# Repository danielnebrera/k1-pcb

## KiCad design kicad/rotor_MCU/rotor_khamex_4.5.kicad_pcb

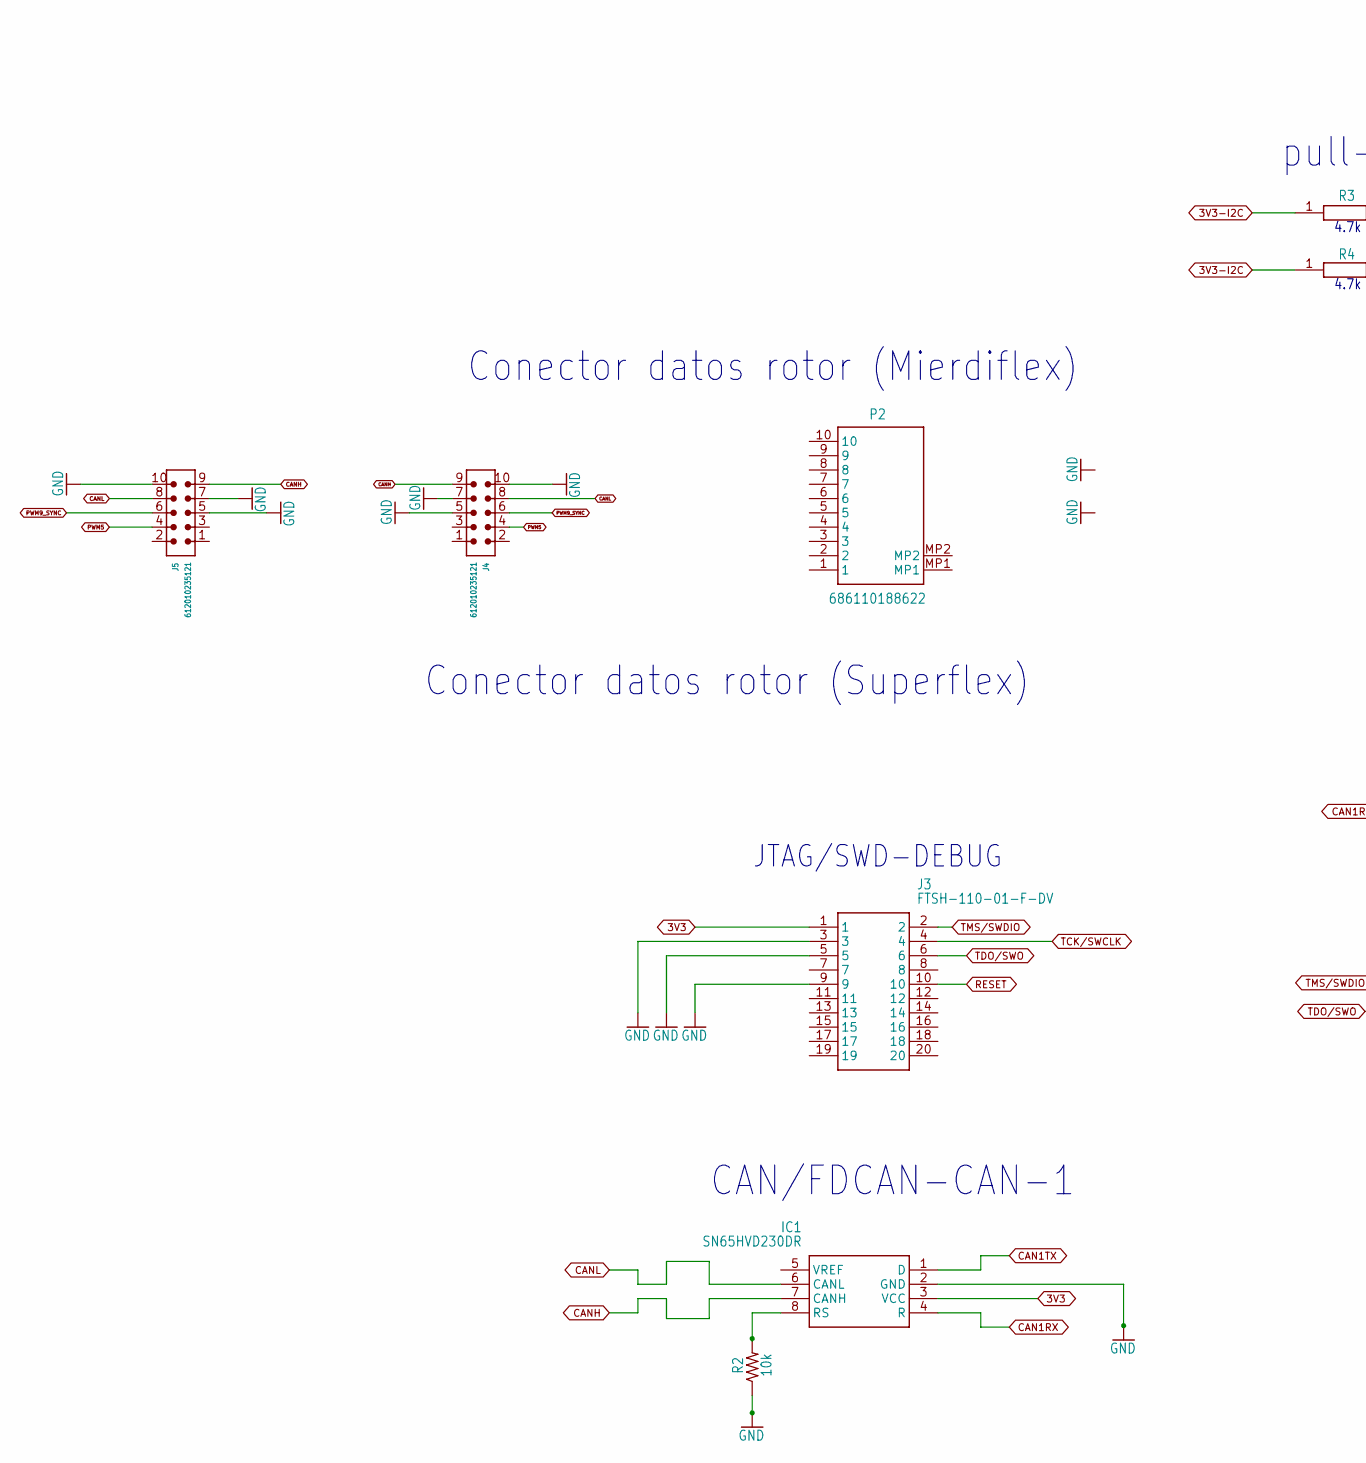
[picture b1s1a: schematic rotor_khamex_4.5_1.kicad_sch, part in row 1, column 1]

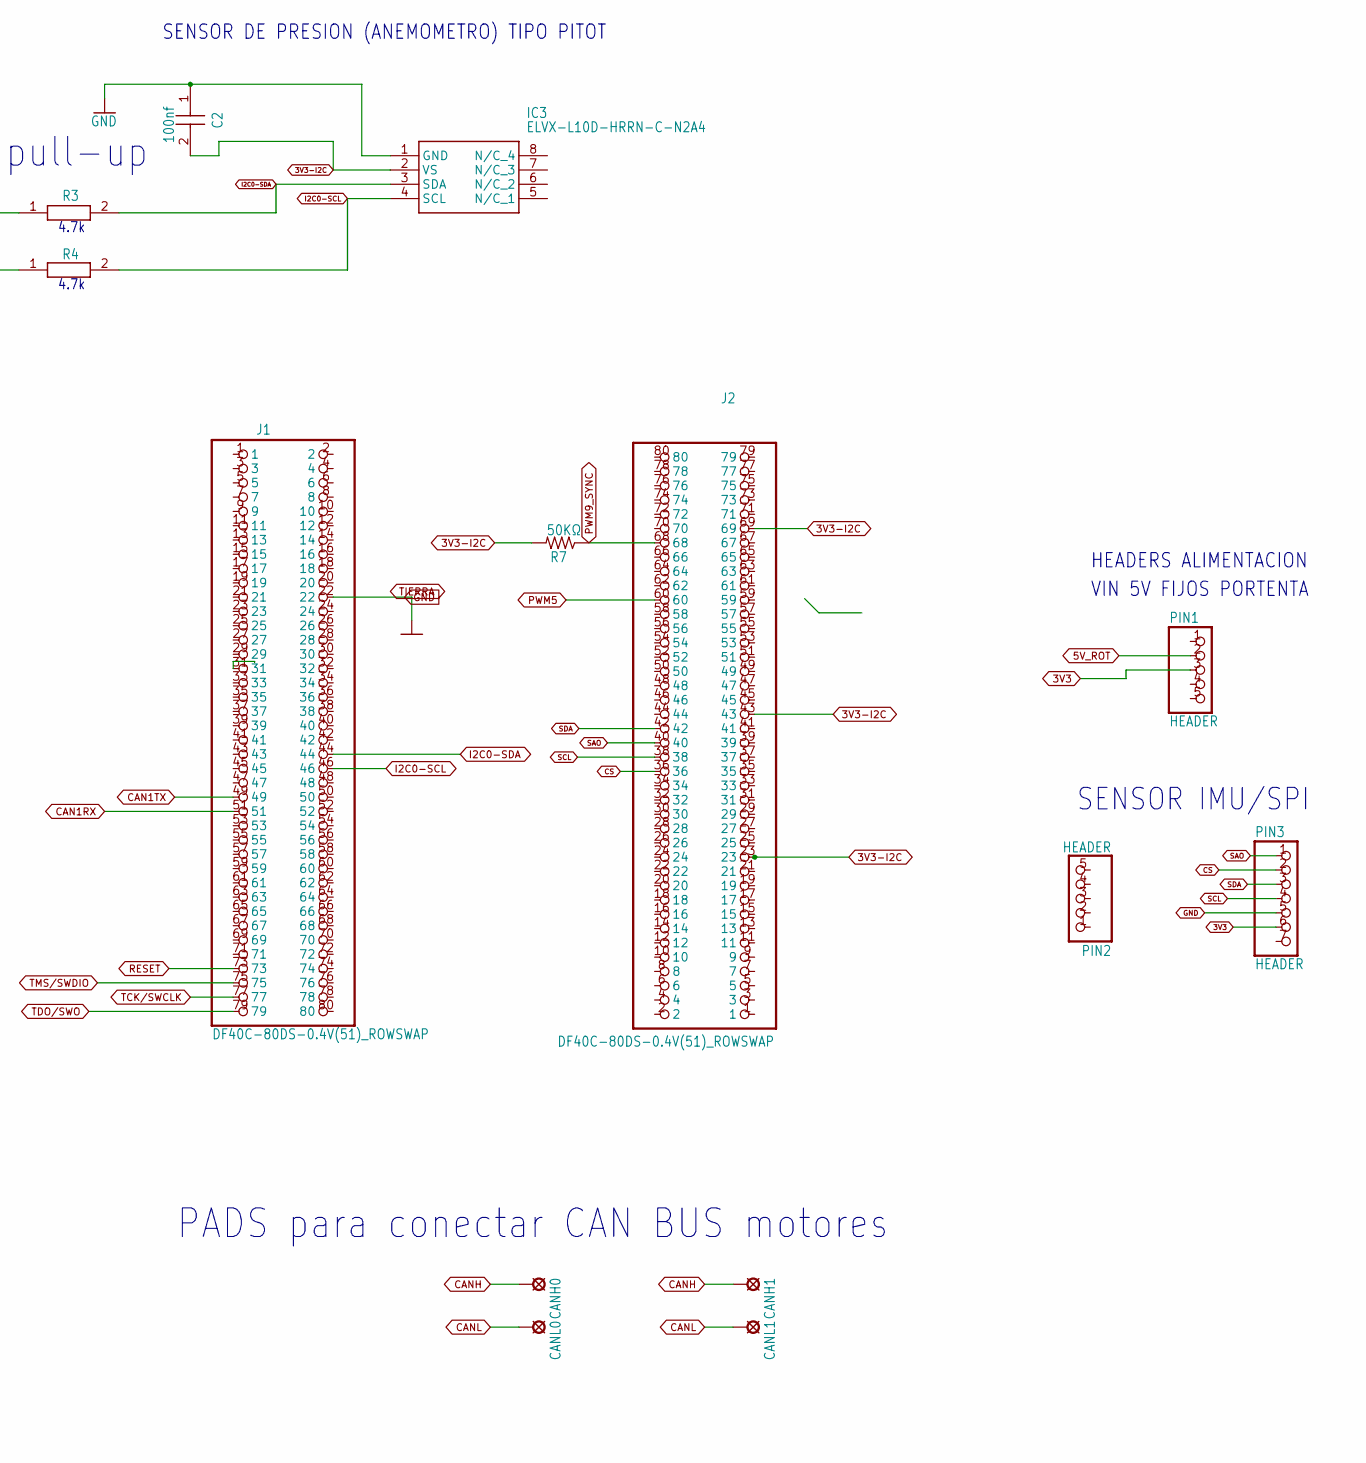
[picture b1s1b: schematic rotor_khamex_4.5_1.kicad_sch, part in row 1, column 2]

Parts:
C2: 100nf; CAPC2012X145N
CANH0, CANH1: LSP11
CANL0, CANL1: LSP11
IC1: SN65HVD230DR; SOT127P600X175-8N
IC3: ELVX-L10D-HRRN-C-N2A4; ELVXL10DHRRNCN2A4
J1, J2: DF40C-80DS-0.4V(51)_ROWSWAP; HRS_DF40C-80DS-0.4V(51)_ROWSWAP
J3: FTSH-110-01-F-DV; FTSH-110-XX-YYY-DV
J4, J5: 612010235121
P2: 686110188622
PIN1, PIN2: HEADER; 1X05
PIN3: HEADER; 1X07
R2: 10k; M0805
R3, R4: 4.7k; RESC2012X50N
R7: 50KΩ; M0805

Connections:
3V3: IC1.3 (VCC), J3.1, PIN1.3, PIN3.6
3V3-I2C: C2.2, IC3.2 (VS), J2.23, J2.43, J2.69, R3.1, R4.1, R7.2
5V_ROT: PIN1.2; also elsewhere on the board
CAN1RX: IC1.4 (R), J1.51
CAN1TX: IC1.1 (D), J1.49
CANH: CANH0.MP, CANH1.MP, IC1.7 (CANH), J4.9, J5.9
CANL: CANL0.MP, CANL1.MP, IC1.6 (CANL), J4.8, J5.8
CS: J2.36, PIN3.2
I2C0-SCL: IC3.4 (SCL), J1.46, R4.2
I2C0-SDA: IC3.3 (SDA), J1.44, R3.2
unnamed: IC1.8 (RS), R2.2
PWM5: J2.60, J4.4, J5.4
PWM9_SYNC: J2.68, J4.6, J5.6, R7.1
RESET: J1.73, J3.10
SAO: J2.40, PIN3.1
SCL: J2.38, PIN3.4
SDA: J2.42, PIN3.3
TCK/SWCLK: J1.77, J3.4
TDO/SWO: J1.79, J3.6
TMS/SWDIO: J1.75, J3.2

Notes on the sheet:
VIN 5V FIJOS PORTENTA
HEADERS ALIMENTACION
4.7k
Conector datos rotor (Superflex)
JTAG/SWD-DEBUG
PADS para conectar CAN BUS motores
Conector datos rotor (Mierdiflex)
SENSOR DE PRESION (ANEMOMETRO) TIPO PITOT
CAN/FDCAN-CAN-1
pull-up
SENSOR IMU/SPI

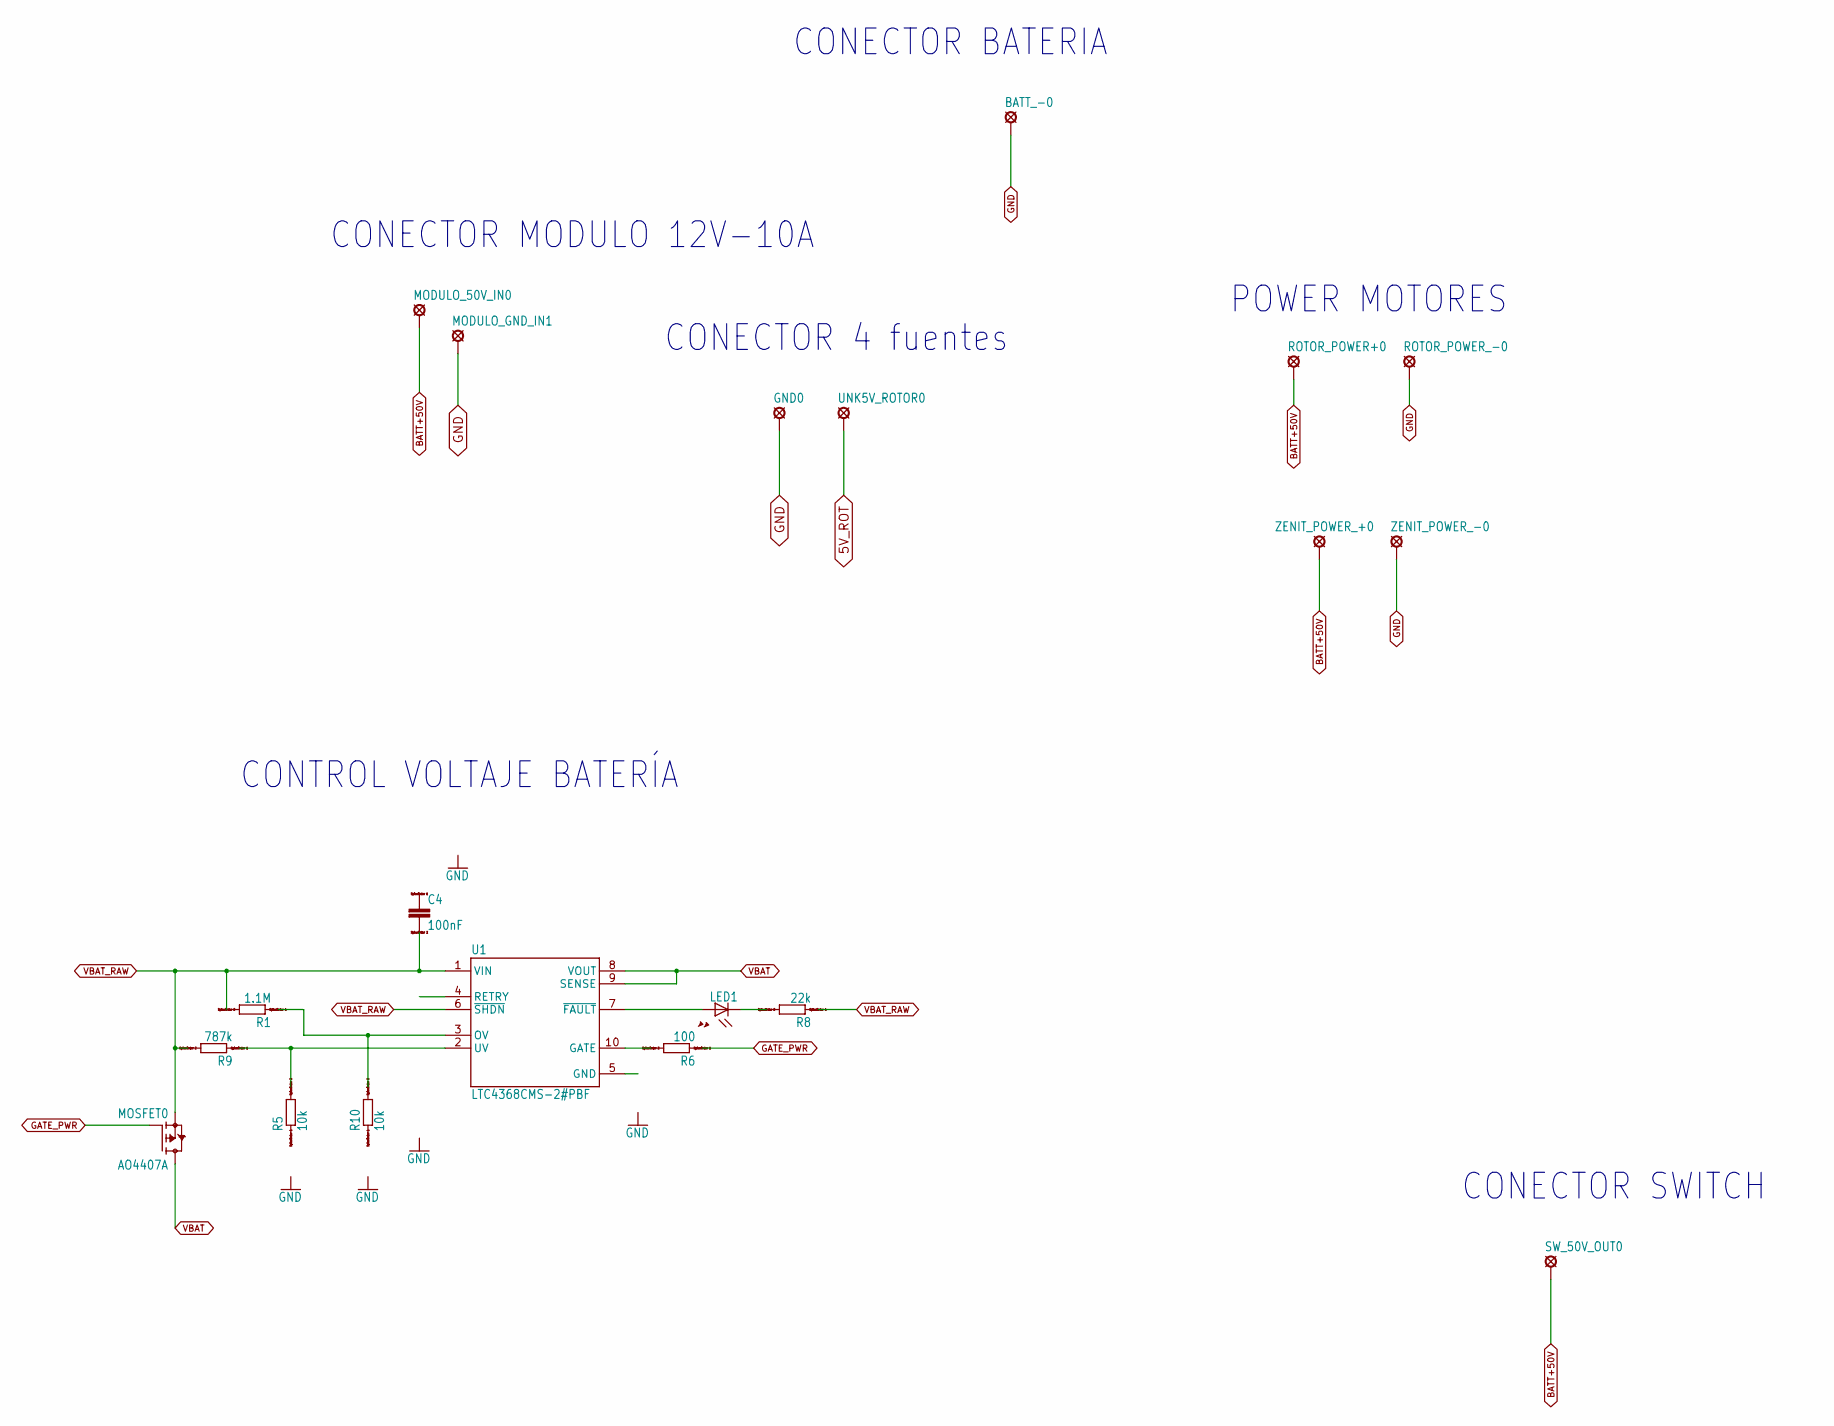
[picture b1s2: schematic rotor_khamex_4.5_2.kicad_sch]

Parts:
BATT_-0: SE14
C4: 100nF; C0805
GND0: SE14
LED1: LED; SMARTLED-TTW
MODULO_50V_IN0: SE14
MODULO_GND_IN1: SE14
MOSFET0: AO4407A; SOIC127P600X175-8N
R1: 1.1M; R0805
R5, R10: 10k; R0805
R6: 100; R0805
R8: 22k; R0805
R9: 787k; R0805
ROTOR_POWER+0: SE14
ROTOR_POWER_-0: SE14
SW_50V_OUT0: SE14
U1: LTC4368CMS-2#PBF; SOP50P490X110-10N
UNK5V_ROTOR0: SE14
ZENIT_POWER_+0: SE14
ZENIT_POWER_-0: SE14

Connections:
5V_ROT: UNK5V_ROTOR0.MP; also elsewhere on the board
BATT+50V: MODULO_50V_IN0.MP, ROTOR_POWER+0.MP, SW_50V_OUT0.MP, ZENIT_POWER_+0.MP
GATE_PWR: MOSFET0.4 (G), R6.1
unnamed: LED1.A@1 (A), U1.7 (~FAULT)
unnamed: R5.2, R9.1, U1.2 (UV)
unnamed: R1.1, R10.2, U1.3 (OV)
unnamed: LED1.C@1 (C), R8.2
unnamed: R6.2, U1.10 (GATE)
VBAT: MOSFET0.5 (D), MOSFET0.6 (D), MOSFET0.7 (D), MOSFET0.8 (D), U1.8 (VOUT), U1.9 (SENSE)
VBAT_RAW: C4.2, MOSFET0.1 (S), MOSFET0.2 (S), MOSFET0.3 (S), R1.2, R8.1, R9.2, U1.1 (VIN), U1.6 (~SHDN)

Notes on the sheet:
CONTROL VOLTAJE BATERÍA
CONECTOR 4 fuentes
CONECTOR SWITCH
POWER MOTORES
CONECTOR MODULO 12V-10A
CONECTOR BATERIA

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
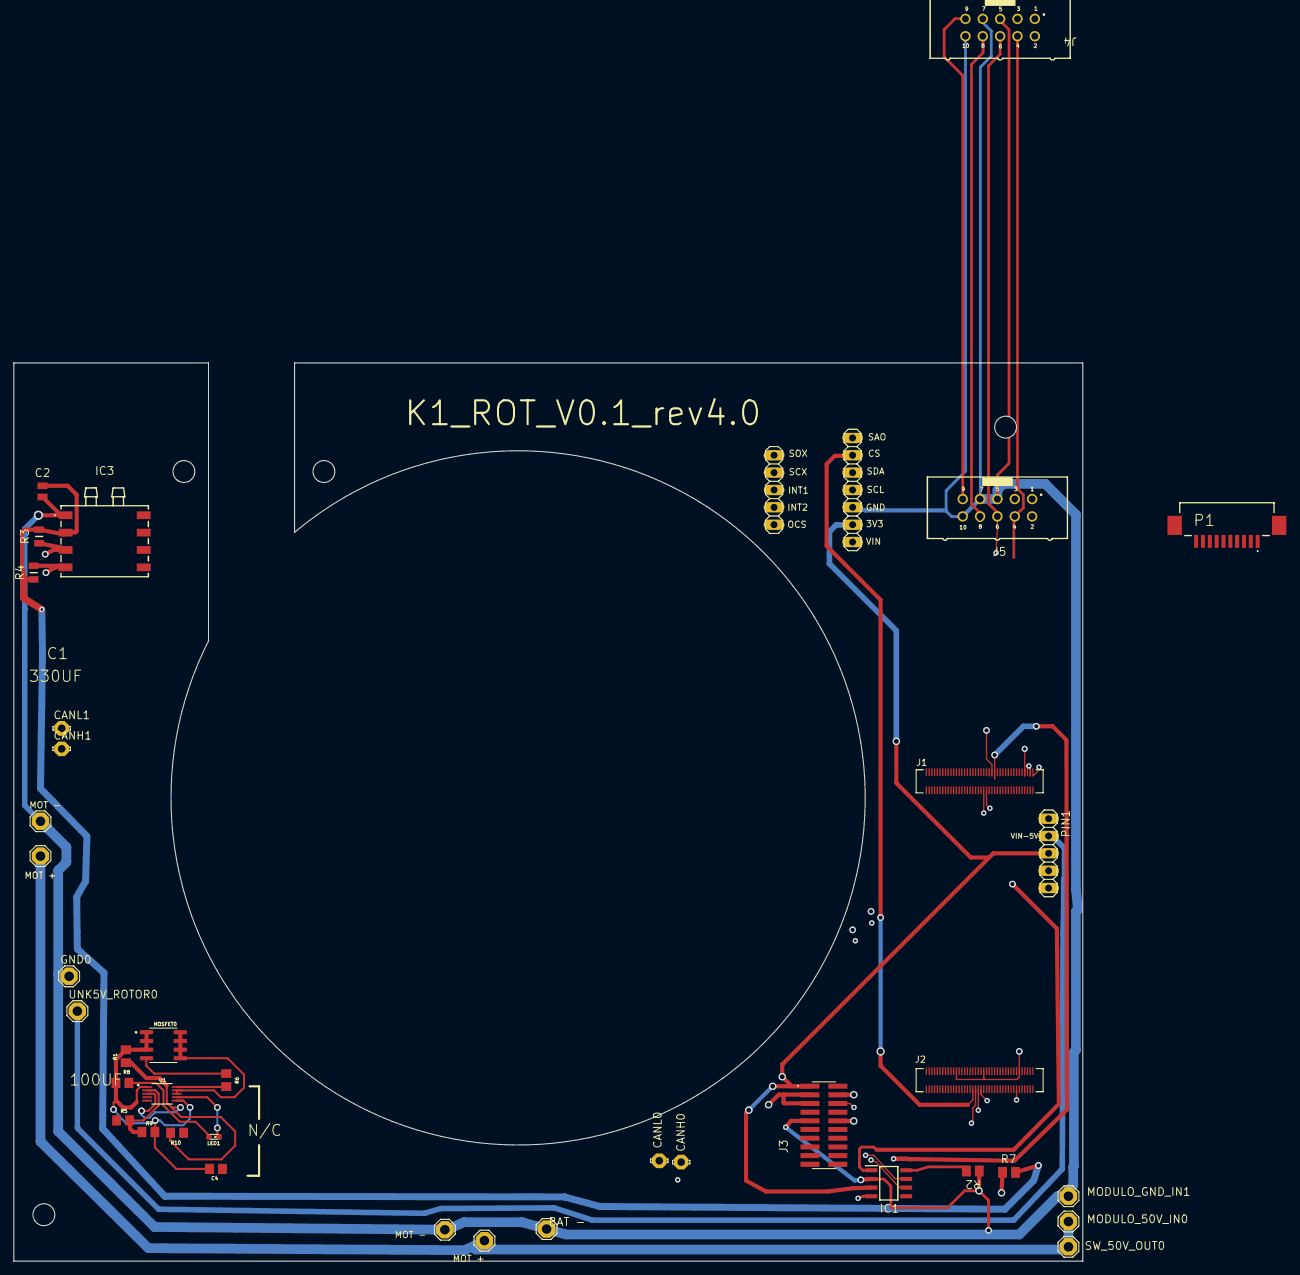
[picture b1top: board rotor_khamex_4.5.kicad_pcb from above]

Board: 4 copper layers, 156.5 x 131.5 mm, 44 parts (0 on the bottom side), 30 nets.

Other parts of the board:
UNK_HOLE_0: dummyfp0
UNK_HOLE_1: dummyfp1
UNK_HOLE_2: dummyfp2
UNK_HOLE_3: dummyfp3
